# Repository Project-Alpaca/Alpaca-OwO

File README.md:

# Alpaca-OwO

Obtainable w/ rOna I/O board.

## Features

- Familiar form factor
- Removable screw terminals makes reconnecting buttons more convenient
  - Tool-less spring terminal option available (when using Phoenix 1952348)
- Rich I/O
  - Analog stick port
  - Simultaneous access to hardware SPI, I2C and basic UART via EXT port
  - SparkFun Qwiic/Adafruit STEMMA-QT compatible I2C quick connect port
  - Possibility to support various proprietary gamepad/joystick interfaces with RP2040 PIO and spare GPIO on EXT port

## Pin assignments

Below is the preferred pin assignment for this board. Note that every pin can be remapped or re-purposed when necessary and this list only serves as a guideline. Still, follow this list when developing firmware if you wish to keep wiring compatibility with other fightstick PCBs and preserve the meaning of the silk screens.

### Pluggable terminal ports

| RP2040 Pin | GP2040 Pin | Label | Purpose |
| ---------- | ---------- | ----- | ------- |
| 0 | DPad Down | D | D-Button Down |
| 1 | DPad Up | U | D-Button Up |
| 2 | DPad Left | L | D-Button Left |
| 3 | DPad Right | R | D-Button Right |
| 4 | A1 | PS | PS Button |
| 5 | S1 | SHR | Share Button |
| 6 | S2 | OPT | Option Button |
| 7 | B3 | SQR | Square Button |
| 8 | B4 | TRI | Triangle Button |
| 9 | R1 | R1 |R1 Button |
| 10 | L1 | L1 | L1 Button |
| 11 | B1 | XRO | Cross Button |
| 12 | B2 | CIR | Circle Button |
| 13 | R2 | R2 | R2 Button |
| 14 | L2 | L2 | L2 Button |

### Ext port, I2C quick connect and analog stick port

| RP2040 Pin | GP2040 Pin | Label | Purpose |
| ---------- | ---------- | ----- | ------- |
| 15 | A2 | TP | Touchpad Click Button |
| 16 | - | DI | SPI0 DI |
| 17 | - | CS | SPI0 CS |
| 18 | - | CLK | SPI0 CLK |
| 19 | - | DO | SPI0 DO |
| 20 | - | TX | UART1 TX |
| 21 | - | EXT/RX | UART1 RX |
| 22 | R3 | R3 | R3 Button |
| 23 | L3 | L3 | L3 Button |
| 24 | Display | SDA | I2C0 SDA |
| 25 | Display | SCL | I2C0 SCL |
| 26/ADC0 | - | RY | Analog Stick RY |
| 27/ADC1 | - | Stick/RX | Analog Stick RX |
| 28/ADC2 | - | LY | Analog Stick LY |
| 29/ADC3 | - | LX | Analog Stick LX |

## Terminal block options

Any pluggable terminal block plugs that mate with a Phoenix MINI COMBICON MC terminal block header should be usable with Alpaca-OwO. Notable configurations include the [basic screw terminal (1840447)](https://www.phoenixcontact.com/en-us/products/pcb-plug-mc-1510-st-35-1840447), the [tool-less spring terminal (1939989)](https://www.phoenixcontact.com/en-us/products/pcb-plug-fk-mcp-1510-st-35-1939989) and the [low profile spring terminal (1952348)](https://www.phoenixcontact.com/en-us/products/pcb-plug-fmc-1510-st-35-1952348). Generic replacements of these connectors can be found on Aliexpress or LCSC. Note that the locking variants will not fit and thus not supported.

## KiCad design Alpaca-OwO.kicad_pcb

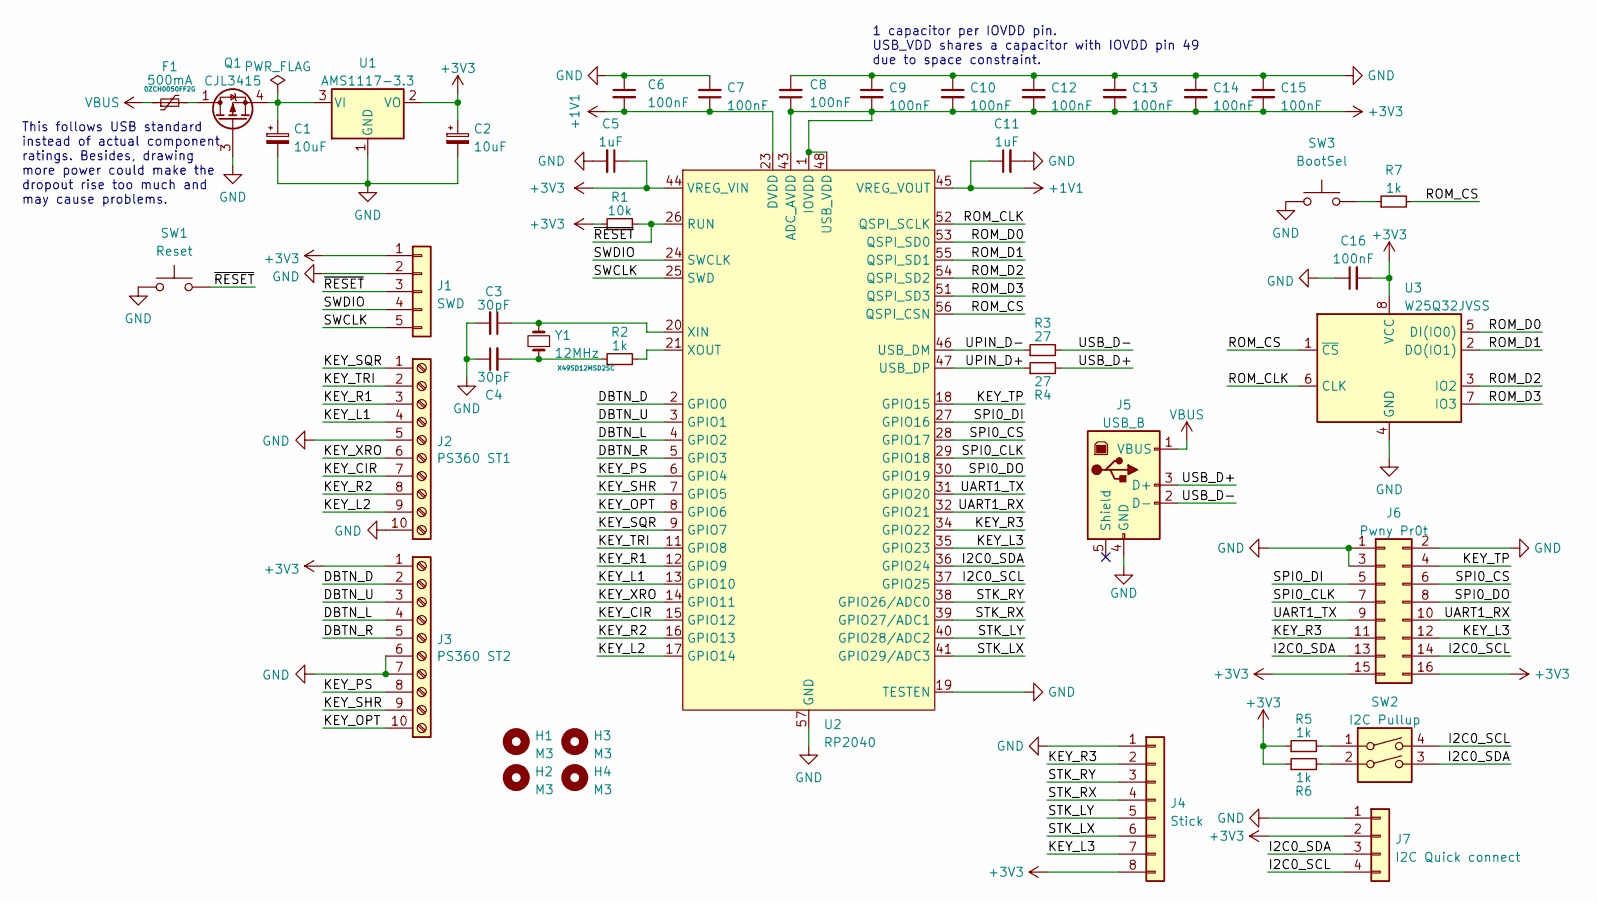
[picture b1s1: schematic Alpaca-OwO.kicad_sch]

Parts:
C1, C2: 10uF; CP_EIA-3216-18_Kemet-A; JLC CASE-A_3216
C3, C4: 30pF; C_0603_1608Metric; JLC 0603
C5, C11: 1uF; C_0603_1608Metric; JLC 0603
C6, C7, C8, C9, C10, C12, C13, C14, C15, C16: 100nF; C_0603_1608Metric; JLC 0603
F1: 500mA; Fuse_1210_3225Metric; Part Number 0ZCH0050FF2G; LCSC C135348
H1, H2, H3, H4: M3; MountingHole_3.2mm_M3_ISO7380
J1: SWD; PinHeader_1x05_P2.54mm_Vertical; JLC Plugin,P=2.54mm
J2: PS360 ST1; PhoenixContact_MC_1,5_10-G-3.5_1x10_P3.50mm_Horizontal; JLC P=3.5mm
J3: PS360 ST2; PhoenixContact_MC_1,5_10-G-3.5_1x10_P3.50mm_Horizontal; JLC P=3.5mm
J4: Stick; PinHeader_1x08_P2.54mm_Vertical; JLC Plugin,P=2.54mm
J5: USB_B; USB_B_OST_USB-B1HSxx_Horizontal; JLC Plugin
J6: Pwny Pr0t; PinHeader_2x08_P2.54mm_Vertical; JLC Plugin,P=2.54mm
J7: I2C Quick connect; JST_SH_SM04B-SRSS-TB_1x04-1MP_P1.00mm_Horizontal; LCSC C160404
Q1: CJL3415; SOT-23-6; LCSC C114069
R1: 10k; R_0603_1608Metric; JLC 0603
R2, R5, R6, R7: 1k; R_0603_1608Metric; JLC 0603
R3, R4: 27; R_0603_1608Metric; JLC 0603
SW1: Reset; SW_PUSH_6mm; JLC Plugin
SW2: I2C Pullup; SW_DIP_SPSTx02_Slide_9.78x7.26mm_W7.62mm_P2.54mm; JLC Plugin
SW3: BootSel; SW_PUSH_6mm; JLC Plugin
U1: AMS1117-3.3; SOT-223-3_TabPin2; JLC SOT-223
U2: RP2040; QFN-56-1EP_7x7mm_P0.4mm_EP3.2x3.2mm_ThermalVias; JLC QFN-56(7x7)
U3: W25Q32JVSS; SOIC-8_5.23x5.23mm_P1.27mm; JLC SOIC-8_208mil
Y1: 12MHz; Crystal_HC49-4H_Vertical; Part Number X49SD12MSD2SC; JLC HC-49S

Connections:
+1V1: C6.2, C7.1, C11.1, U2.23 (DVDD), U2.45 (VREG_VOUT), U2.50 (DVDD)
+3V3: C2.1, C5.1, C8.1, C9.2, C10.2, C12.2, C13.2, C14.2, C15.2, C16.2, J1.1, J3.1, J4.8, J6.15, J6.16, J7.2, R1.1, R5.1, R6.1, U1.2 (VO), U2.1 (IOVDD), U2.10 (IOVDD), U2.22 (IOVDD), U2.33 (IOVDD), U2.42 (IOVDD), U2.43 (ADC_AVDD), U2.44 (VREG_VIN), U2.48 (USB_VDD), U2.49 (IOVDD), U3.8 (VCC)
/DBTN_D: J3.2, U2.2 (GPIO0)
/DBTN_L: J3.4, U2.4 (GPIO2)
/DBTN_R: J3.5, U2.5 (GPIO3)
/DBTN_U: J3.3, U2.3 (GPIO1)
/I2C0_SCL: J6.14, J7.4, SW2.4, U2.37 (GPIO25)
/I2C0_SDA: J6.13, J7.3, SW2.3, U2.36 (GPIO24)
/KEY_CIR: J2.7, U2.15 (GPIO12)
/KEY_L1: J2.4, U2.13 (GPIO10)
/KEY_L2: J2.9, U2.17 (GPIO14)
/KEY_L3: J4.7, J6.12, U2.35 (GPIO23)
/KEY_OPT: J3.10, U2.8 (GPIO6)
/KEY_PS: J3.8, U2.6 (GPIO4)
/KEY_R1: J2.3, U2.12 (GPIO9)
/KEY_R2: J2.8, U2.16 (GPIO13)
/KEY_R3: J4.2, J6.11, U2.34 (GPIO22)
/KEY_SHR: J3.9, U2.7 (GPIO5)
/KEY_SQR: J2.1, U2.9 (GPIO7)
/KEY_TP: J6.4, U2.18 (GPIO15)
/KEY_TRI: J2.2, U2.11 (GPIO8)
/KEY_XRO: J2.6, U2.14 (GPIO11)
/ROM_CLK: U2.52 (QSPI_SCLK), U3.6 (CLK)
/ROM_CS: R7.2, U2.56 (QSPI_CSN), U3.1 (~CS)
/ROM_D0: U2.53 (QSPI_SD0), U3.5 (DI(IO0))
/ROM_D1: U2.55 (QSPI_SD1), U3.2 (DO(IO1))
/ROM_D2: U2.54 (QSPI_SD2), U3.3 (IO2)
/ROM_D3: U2.51 (QSPI_SD3), U3.7 (IO3)
/SPI0_CLK: J6.7, U2.29 (GPIO18)
/SPI0_CS: J6.6, U2.28 (GPIO17)
/SPI0_DI: J6.5, U2.27 (GPIO16)
/SPI0_DO: J6.8, U2.30 (GPIO19)
/STK_LX: J4.6, U2.41 (GPIO29/ADC3)
/STK_LY: J4.5, U2.40 (GPIO28/ADC2)
/STK_RX: J4.4, U2.39 (GPIO27/ADC1)
/STK_RY: J4.3, U2.38 (GPIO26/ADC0)
/SWCLK: J1.5, U2.25 (SWD)
/SWDIO: J1.4, U2.24 (SWCLK)
/UART1_RX: J6.10, U2.32 (GPIO21)
/UART1_TX: J6.9, U2.31 (GPIO20)
/UPIN_D+: R4.1, U2.47 (USB_DP)
/UPIN_D-: R3.1, U2.46 (USB_DM)
/USB_D+: J5.3 (D+), R4.2
/USB_D-: J5.2 (D-), R3.2
/~RESET: J1.3, R1.2, SW1.1, U2.26 (RUN)
GND: C1.2, C2.2, C3.2, C4.1, C5.2, C6.1, C7.2, C8.2, C9.1, C10.1, C11.2, C12.1, C13.1, C14.1, C15.1, C16.1, J1.2, J2.5, J2.10, J3.6, J3.7, J4.1, J5.4 (GND), J6.1, J6.2, J6.3, J7.1, Q1.3 (G), SW1.2, SW3.2, U1.1 (GND), U2.19 (TESTEN), U2.57 (GND), U3.4 (GND)
unnamed: C1.1, Q1.4 (S), U1.3 (VI)
unnamed: C3.1, U2.20 (XIN), Y1.2
unnamed: C4.2, R2.1, Y1.1
unnamed: F1.2, Q1.1 (D), Q1.2 (D), Q1.5 (D), Q1.6 (D)
unnamed: R2.2, U2.21 (XOUT)
unnamed: R5.2, SW2.1
unnamed: R6.2, SW2.2
unnamed: R7.1, SW3.1
VBUS: F1.1, J5.1 (VBUS)

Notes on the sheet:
This follows USB standard instead of actual component ratings. Besides, drawing more power could make the dropout rise too much and may cause problems.
1 capacitor per IOVDD pin. USB_VDD shares a capacitor with IOVDD pin 49 due to space constraint.

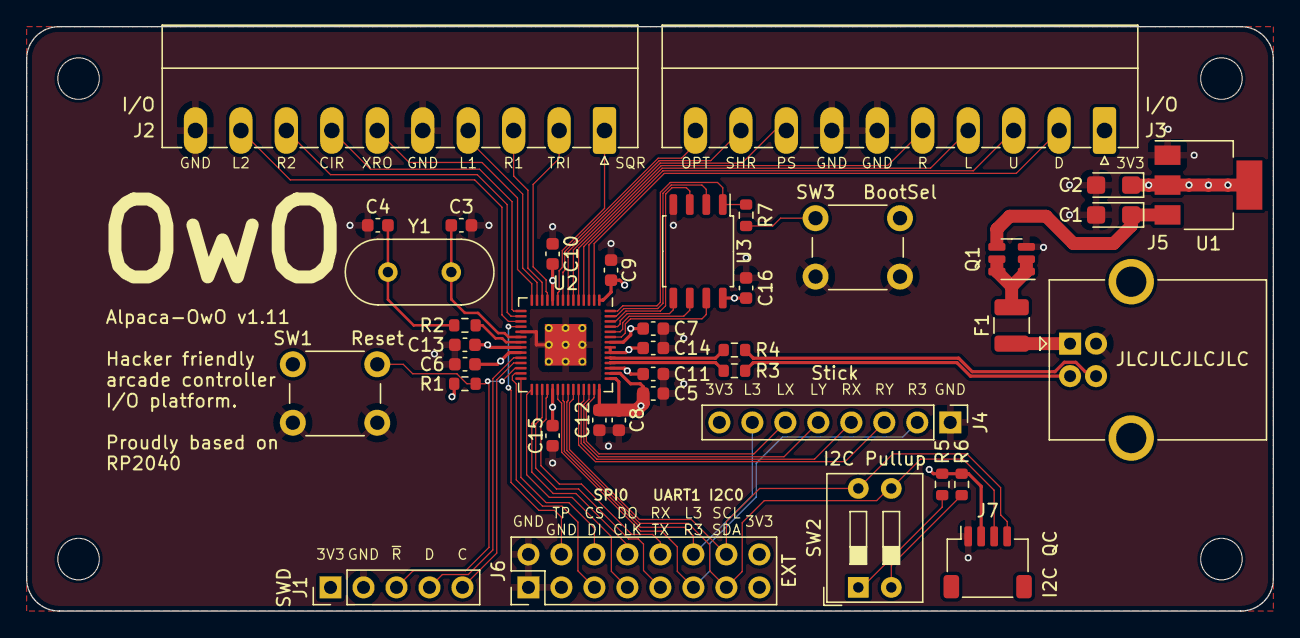
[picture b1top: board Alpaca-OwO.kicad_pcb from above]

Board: 4 copper layers, 96.0 x 45.0 mm, 43 parts (0 on the bottom side), 55 nets.

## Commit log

2022-03-05 Initial commit
    First schematic done. PnR WIP.
2022-03-05 Coarse placement
2022-03-07 Routing checkpoint
2022-03-08 First PnR attempt done.
2022-03-08 More ground vias.
2022-03-08 Fix various issues.
    - USB DM/DP are reversed.
    - Minimum via OD for JLC should be 0.45mm (technically 0.4mm is also accepted but with a big cost penalty).
2022-03-08 Add metadata.
2022-03-08 Add license.
2022-04-11 V1.01 rework.
2022-04-11 Update README.
2022-04-12 Add some PCBA info.
2022-04-13 Flip I2C traces up and some general cleanups
2022-04-13 V1.10 PCB
    Change the via size to be 0.55/0.3 so the annular ring width stay consistent with JLC's design rule.
2022-04-13 Minor track tuning.
2022-04-13 Update preview.
2022-04-14 Import LCSC parts info for all components except pin headers.
2022-04-14 Set screw holes as do not include
2022-04-14 Add more GND vias near components. Update README.
2022-04-17 v1.11
    Fixed an issue where the analog stick port does not follow the Brook pinout.
    No PCB routing was changed but the pin assignment for stick axis and L3/R3 buttons are now mirrored. Refer to README for the new pinout.
2022-05-04 Update preview
2022-05-04 Update silkscreen
2023-06-19 Add more detailed pin assignment info to README
2023-06-19 Disambiguation for RX label
